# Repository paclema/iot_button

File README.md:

# iot_button

## WARNING: _Repository Discontinued_
This repository is now archived and further development is not expected. The repository was initially created as a proof of concept to develop a firmware for ESP8266 and ESP32 devices capable of running a web server stored into the flash memory next to Arduino based firmware code to handle easily internal configurations such as WiFI credentials and connection settings, MQTT, OTA and more services configurations or user custom class configurations. 

This repository has been archived as a result of the creation of the Platformio [WebConfigServer](https://github.com/paclema/WebConfigServer) library.

## Features:

Web application:
* Angular 10 and Bootstrap 4 web application to configure the device and visualize data.
* Nebular UI Angular lib.
* ng2-charts to visualize WS data graphs on dashboard web server endpoint.
* Gzipped compression to store and serve the Webapp.

Firmware:
* ESP32 support.
* Improved platformio targets and ESP partitions for Wemos D1 mini and Lolin D32 pro and OTA updates.
* Store configs as JSON and certs on SPI Flash File System (SPIFFS).
* AP+STA wifi mode with wifimulti and mDNS support
* FTP server to easily modify files stored on SPIFFS.
* WrapperOTA class to handle OTA updates.
* WrapperWebSockets class to handle WS communication between device and webserver dashboard endpoint.
* MQTT client as QoS2 to detect disconnection and enabled connection using user&pass and/or certificates.
* Added configurable DeepSleep modes for ESP8266.
* Webserver or AsyncWebserver support.
* Enabled lwip NAT features for ESP8266 and ESP32.
* Added configurable NTP server.

## Requirements:

* Wemos D1 mini (ESP8266) or Lolin D32 pro (ESP32).
* push button on RST --> this will triger the push action after restart the board.
* D0 (GPIO16) connected to RST so Deep Sleep can wake up after the sleep time configured.
* CHPD (or EN) to VCC.
* Wemos D1 mini can use USB power or 3v3-5v on 5v pin.

### Add a new configuration object:
1. Update the new object in the configuration file _/data/config.json_
2. Add the struct object in the configuration class _/lib/WebConfigServer/WebConfigServer.h_
3. Update the parse function to link the json object with the class struct in the configuration class _/lib/WebConfigServer/WebConfigServer.cpp_

### Upload _/data_ folder to ESP SPIFFS File System:

Using platformio run the next command: `pio run -t uploadfs`

### Build webserver to _/data_ fodler:
If you can not run angular-cli from platformio PowerShell using windows, activate it with:
Set-ExecutionPolicy -ExecutionPolicy RemoteSigned -Scope CurrentUser

Under _webserver/_ folder:
```console
ng build --prod --optimization=true --outputHashing=none; npm run postbuild
```

To build and upload SPIFFS
```console
cd ./webserver; ng build --prod --optimization=true --outputHashing=none; npm run postbuild;cd ..; pio run --target uploadfs --environment d1_mini
```

To build for xammp:
```console
ng build --prod --optimization=true --outputHashing=none --outputPath=C:/xampp/htdocs --deleteOutputPath=false
```

These build options can be added in angular.json in the future.

### Compress _/data_ fodler with gzip:
Under webserver folder:

```console
npm run postbuild
```

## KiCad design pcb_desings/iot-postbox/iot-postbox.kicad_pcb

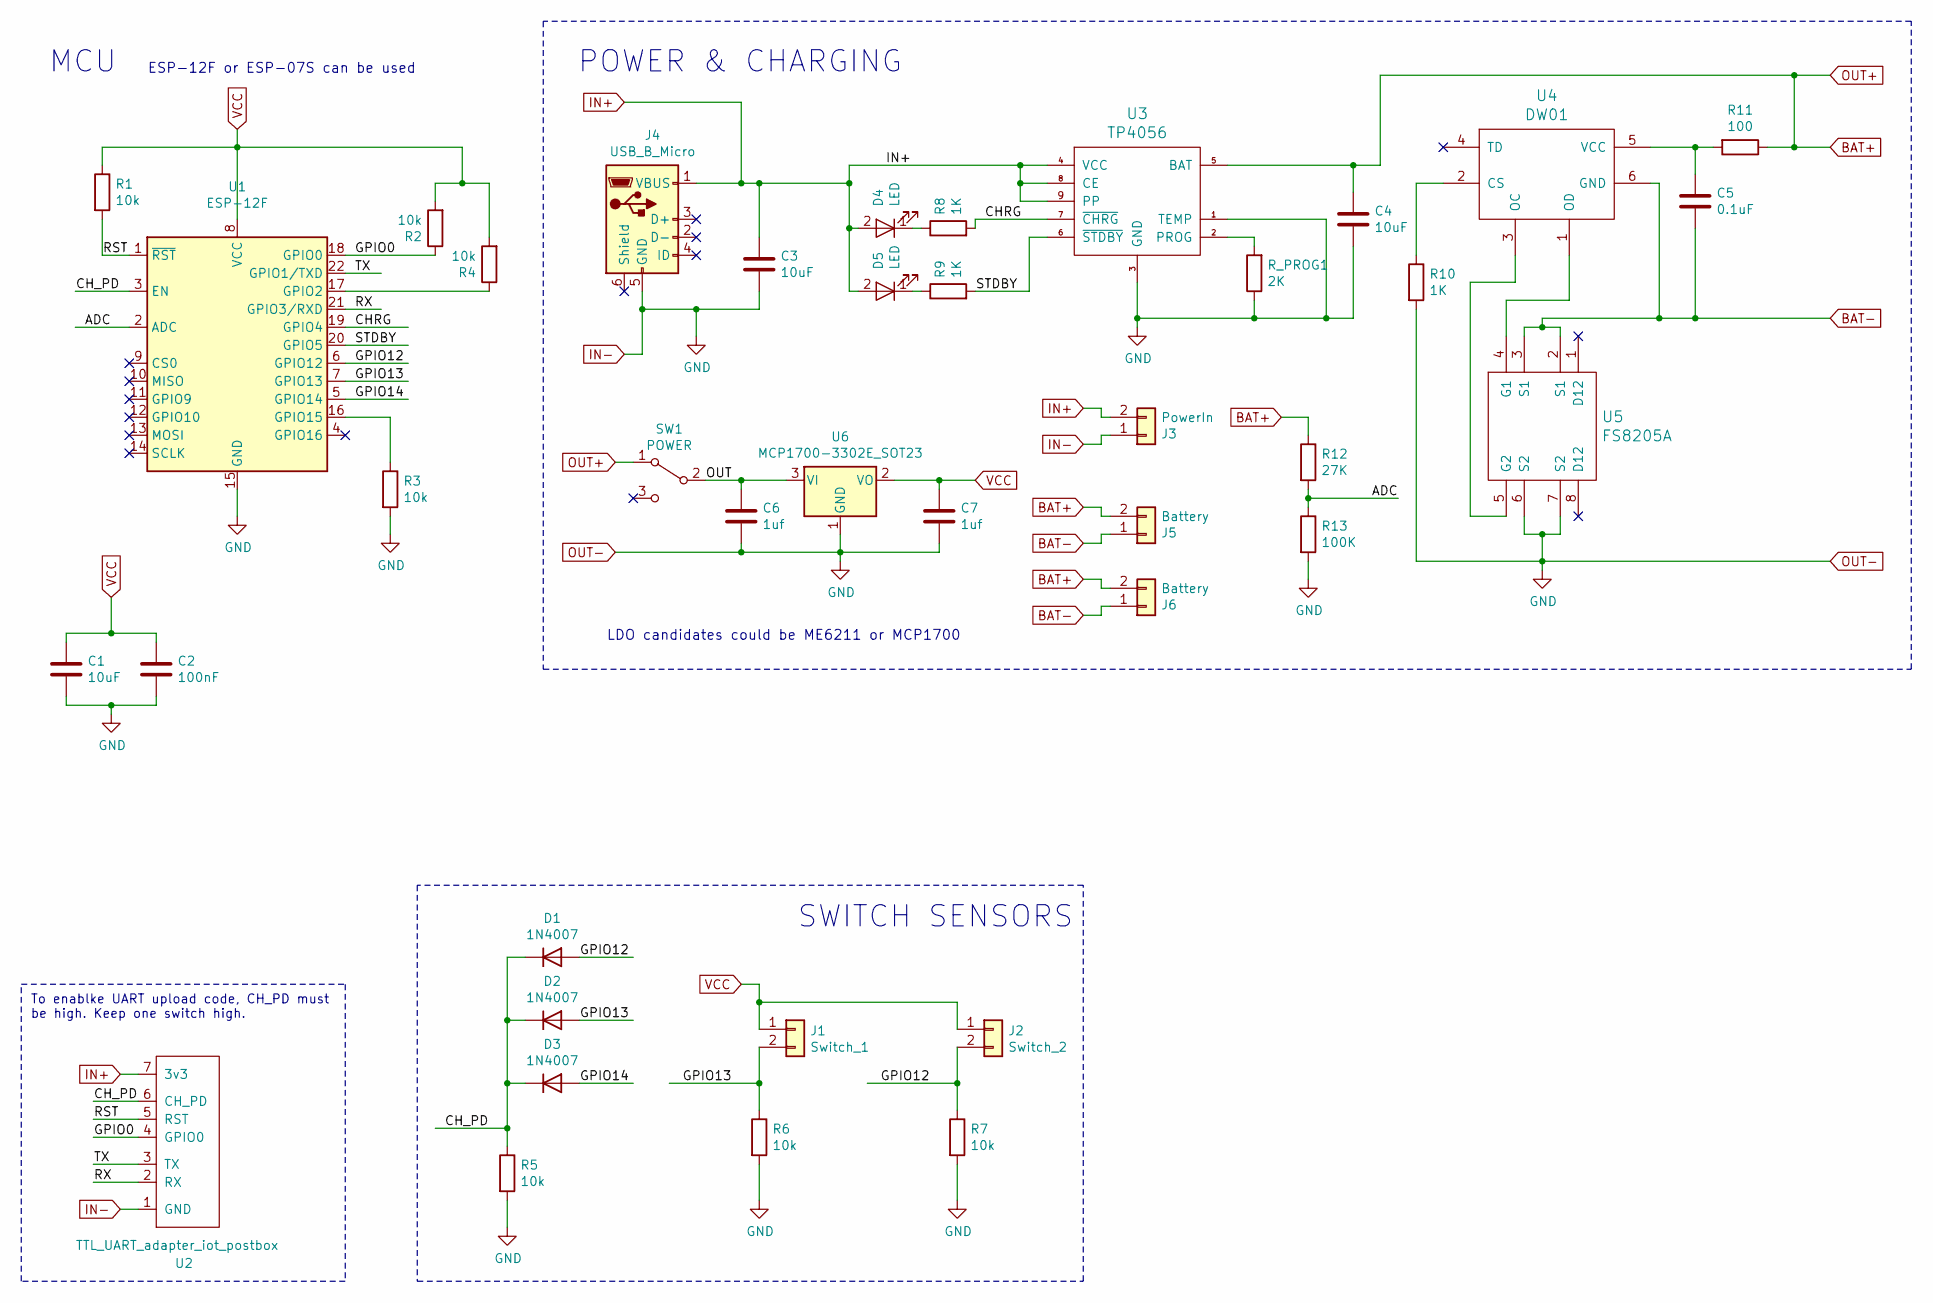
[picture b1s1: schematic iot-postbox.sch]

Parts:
C1, C3, C4: 10uF; C_0805_2012Metric
C2: 100nF; C_0805_2012Metric
C5: 0.1uF; C_0805_2012Metric
C6, C7: 1uf; C_0805_2012Metric
D1, D2, D3: 1N4007; D_SOD-123
D4, D5: LED; LED_0805_2012Metric
J1: Switch_1; PinHeader_1x02_P2.54mm_Vertical
J2: Switch_2; PinHeader_1x02_P2.54mm_Vertical
J3: PowerIn; PinHeader_1x02_P2.54mm_Vertical
J4: USB_B_Micro; USB_Micro-B_Amphenol_10118194_Horizontal
J5: Battery; JST_PH_S2B-PH-SM4-TB_1x02-1MP_P2.00mm_Horizontal
J6: Battery; PinHeader_1x02_P2.54mm_Vertical
R1, R2, R3, R4, R5, R6, R7: 10k; R_0805_2012Metric
R8, R9, R10: 1K; R_0805_2012Metric
R11: 100; R_0805_2012Metric
R12: 27K; R_0805_2012Metric
R13: 100K; R_0805_2012Metric
R_PROG1: 2K; R_0805_2012Metric
SW1: POWER; 1P2T_SPDT_MSK-C02_7pin
U1: ESP-12F; ESP-12E
U2: TTL_UART_adapter_iot_postbox; PinHeader_1x07_P2.54mm_Vertical
U3: TP4056; TP4056_SOP-8-PP
U4: DW01; SOT-23-6_Handsoldering
U5: FS8205A; TSSOP-8_4.4x3mm_P0.65mm
U6: MCP1700-3302E_SOT23; SOT-23

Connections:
/ADC: R12.2, R13.1, U1.2 (ADC)
/CHRG: R8.2, U1.19 (GPIO4), U3.7 (~CHRG)
/CH_PD: D1.1 (K), D2.1 (K), D3.1 (K), R5.1, U1.3 (EN), U2.6 (CH_PD)
/GPIO0: R2.1, U1.18 (GPIO0), U2.4 (GPIO0)
/GPIO12: D1.2 (A), J2.2, R7.1, U1.6 (GPIO12)
/GPIO13: D2.2 (A), J1.2, R6.1, U1.7 (GPIO13)
/GPIO14: D3.2 (A), U1.5 (GPIO14)
/OUT: C6.1, SW1.2 (B), U6.3 (VI)
/RST: R1.2, U1.1 (~RST), U2.5 (RST)
/RX: U1.21 (GPIO3/RXD), U2.2 (RX)
/STDBY: R9.2, U1.20 (GPIO5), U3.6 (~STDBY)
/TX: U1.22 (GPIO1/TXD), U2.3 (TX)
BAT+: C4.1, J5.2, J6.2, R11.1, R12.1, SW1.1 (A), U3.5 (BAT)
BAT-: C5.2, J5.1, J6.1, U4.6 (GND), U5.2 (S1), U5.3 (S1)
IN+: C3.1, D4.2 (A), D5.2 (A), J3.2, J4.1 (VBUS), U2.7 (3v3), U3.4 (VCC), U3.8 (CE), U3.9 (PP); also elsewhere on the board
IN-: C1.2, C2.2, C3.2, C4.2, C6.2, C7.2, J3.1, J4.5 (GND), R3.2, R5.2, R6.2, R7.2, R10.2, R13.2, R_PROG1.1, U1.15 (GND), U2.1 (GND), U3.1 (TEMP), U3.3 (GND), U5.6 (S2), U5.7 (S2), U6.1 (GND)
unnamed: C5.1, R11.2, U4.5 (VCC)
unnamed 17: D4.1 (K), R8.1; also elsewhere on the board
unnamed 18: D5.1 (K), R9.1; also elsewhere on the board
unnamed: R3.1, U1.16 (GPIO15)
unnamed: R4.1, U1.17 (GPIO2)
unnamed: R10.1, U4.2 (CS)
unnamed: R_PROG1.2, U3.2 (PROG)
unnamed: U4.1 (OD), U5.4 (G1)
unnamed: U4.3 (OC), U5.5 (G2)
VCC: C1.1, C2.1, C7.1, J1.1, J2.1, R1.1, R2.2, R4.2, U1.8 (VCC), U6.2 (VO)

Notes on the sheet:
To enablke UART upload code, CH_PD must be high. Keep one switch high.
POWER & CHARGING
SWITCH SENSORS
MCU
ESP-12F or ESP-07S can be used
LDO candidates could be ME6211 or MCP1700

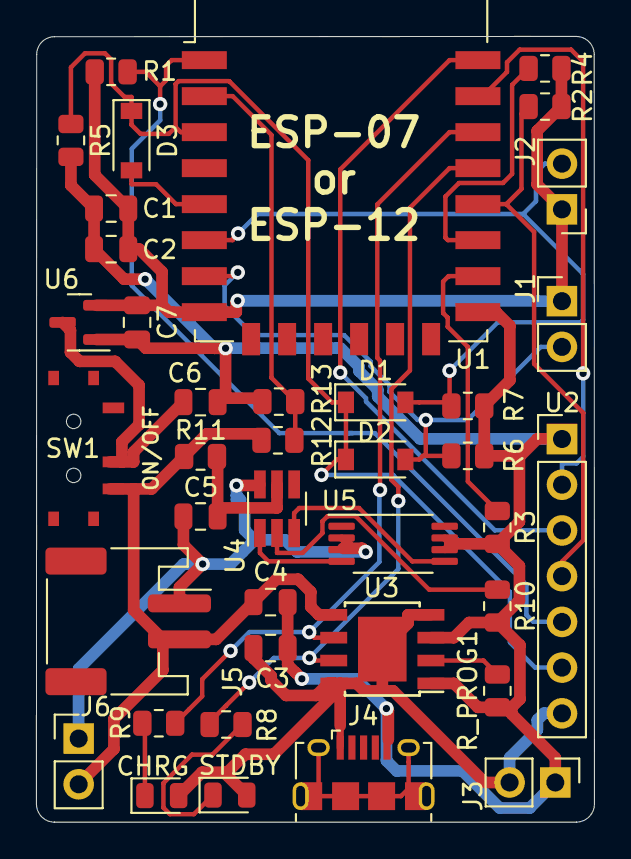
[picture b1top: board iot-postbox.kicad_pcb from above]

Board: 2 copper layers, 31.0 x 43.6 mm, 39 parts (0 on the bottom side), 26 nets.

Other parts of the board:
CHRG: LED; LED_0805_2012Metric
STDBY: LED; LED_0805_2012Metric

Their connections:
IN+: CHRG.2, STDBY.2; also elsewhere on the board
unnamed 17: STDBY.1; also elsewhere on the board
unnamed 18: CHRG.1; also elsewhere on the board

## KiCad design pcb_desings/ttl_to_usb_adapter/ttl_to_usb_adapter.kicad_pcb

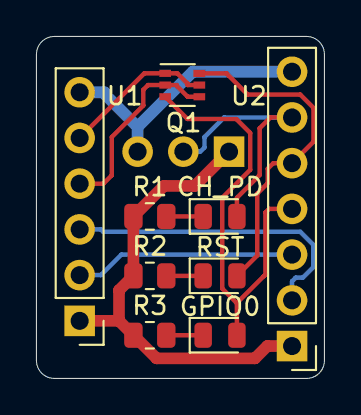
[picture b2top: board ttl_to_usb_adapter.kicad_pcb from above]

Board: 2 copper layers, 16.0 x 19.0 mm, 10 parts (1 on the bottom side), 12 nets.

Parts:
CH_PD: EN; LED_0805_2012Metric
GPIO0: GPIO0; LED_0805_2012Metric
J1: CH_PD_selector; PinHeader_1x03_P2.54mm_Horizontal
Q1: UMH3N; SOT-363_SC-70-6
R1, R2, R3: 68; R_0805_2012Metric
RST: RST; LED_0805_2012Metric
U1: USB_to_TTL; PinHeader_1x06_P2.54mm_Vertical
U2: TTL_UART_adapter_iot_postbox; PinHeader_1x07_P2.54mm_Vertical

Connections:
/3V3: J1.3, U1.6, U2.7
/CH_PD: CH_PD.2, J1.2, U2.6
/DTR: Q1.2, Q1.4, U1.4
/GND: J1.1, R1.1, R2.1, R3.1, U1.1, U2.1
/GPIO0: GPIO0.2, Q1.3, U2.4
/RST: Q1.6, RST.2, U2.5
/RTS: Q1.1, Q1.5, U1.5
/RXD: U1.2, U2.3
/TXD: U1.3, U2.2
unnamed: CH_PD.1, R1.2
unnamed: R2.2, RST.1
unnamed: GPIO0.1, R3.2

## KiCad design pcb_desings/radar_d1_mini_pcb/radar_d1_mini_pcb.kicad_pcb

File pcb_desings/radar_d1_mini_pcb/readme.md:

lib dependencies for kicad:
https://github.com/jerome-labidurie/d1_mini_kicad
https://github.com/rubienr/wemos-d1-mini-kicad
https://kicad.github.io/packages3d/TerminalBlock_Phoenix

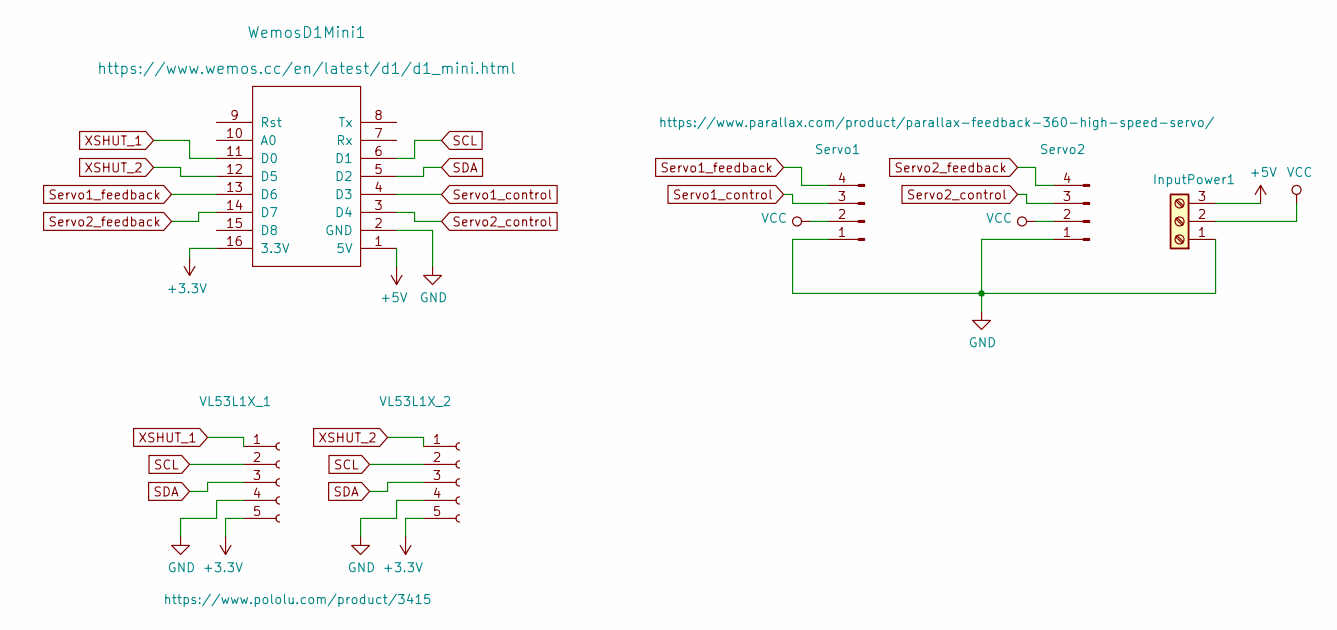
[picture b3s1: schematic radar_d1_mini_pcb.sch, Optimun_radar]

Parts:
InputPower1: Screw_Terminal_01x03; TerminalBlock_Phoenix_MKDS-1,5-3-5.08_1x03_P5.08mm_Horizont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
Servo1, Servo2: Conn_01x04_Male; PinHeader_1x04_P2.54mm_Vertical
VL53L1X_1, VL53L1X_2: Conn_01x05_Female; PinHeader_1x05_P2.54mm_Vertical
WemosD1Mini1: WeMos_D1_mini; D1_mini_board

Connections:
+3V3: VL53L1X_1.5, VL53L1X_2.5, WemosD1Mini1.16 (3.3V)
+5V: InputPower1.3, WemosD1Mini1.1 (5V)
GND: InputPower1.1, Servo1.1, Servo2.1, VL53L1X_1.4, VL53L1X_2.4, WemosD1Mini1.2 (GND)
SCL: VL53L1X_1.2, VL53L1X_2.2, WemosD1Mini1.6 (D1)
SDA: VL53L1X_1.3, VL53L1X_2.3, WemosD1Mini1.5 (D2)
Servo1_control: Servo1.3, WemosD1Mini1.4 (D3)
Servo1_feedback: Servo1.4, WemosD1Mini1.13 (D6)
Servo2_control: Servo2.3, WemosD1Mini1.3 (D4)
Servo2_feedback: Servo2.4, WemosD1Mini1.14 (D7)
VCC: InputPower1.2, Servo1.2, Servo2.2
XSHUT_1: VL53L1X_1.1, WemosD1Mini1.11 (D0)
XSHUT_2: VL53L1X_2.1, WemosD1Mini1.12 (D5)

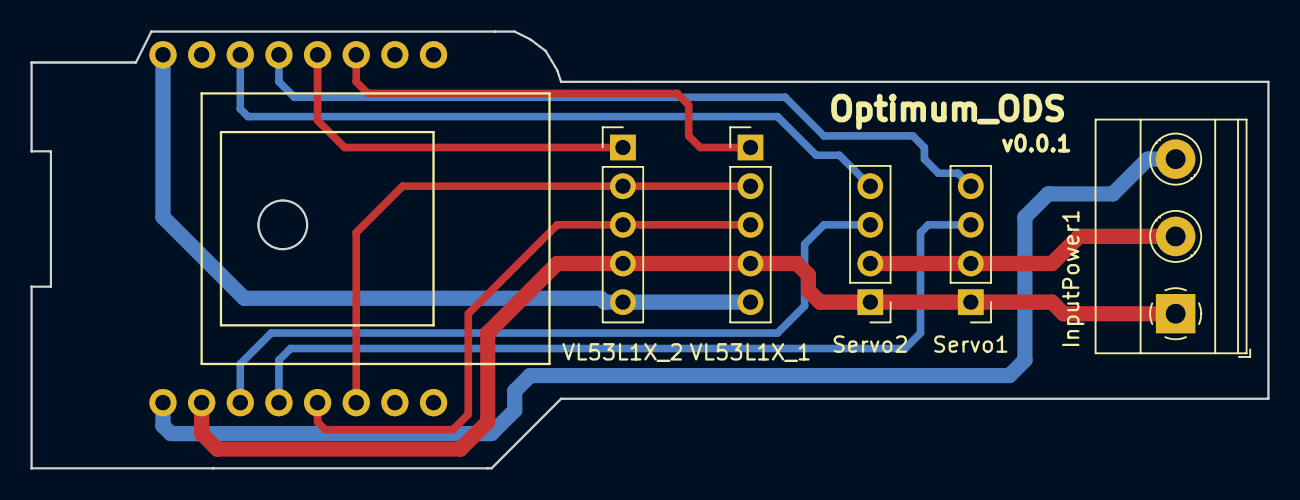
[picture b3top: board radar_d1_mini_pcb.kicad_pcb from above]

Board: 2 copper layers, 81.3 x 28.7 mm, 6 parts (1 on the bottom side), 12 nets.

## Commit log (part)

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2019-06-19 Updated POST for restoreBackup and added file backups management from firmware
2019-06-19 Refactorized code to use WebConfigServer class
2019-06-19 Added favicon on html
2019-06-20 Added ftp server
2019-06-21 Added OTA wrapper class
2019-06-22 Added MQTT client
2019-06-22 toUpperCase first letter for each config name
2019-06-22 Added DeepSleep and LightSleep features
2019-06-22 Code cleaned
2019-06-23 Fixed some variable names and html view for nested objects
2019-06-24 Added platformio lib_deps and moved html deps to upstream
2020-09-03 Replaced SPIFFS deprecated File System to LittleFS
2020-09-04 Updated readme and fixed config ssid variable
2020-09-04 Added AP+STA wifi mode and configs
2020-09-07 Update missing config.json data
2020-09-10 Added loop timers for mqtt publish and sensor reading
2020-09-15 Added VL53L1X readdings
2020-09-16 Added servo control
2020-09-17 Added sensor libraries separatelly for VL53L0X and VL53L1X
2020-09-18 Tried to calculate sensorAngle
2020-09-22 Fixed real angle calculations with servo position
2020-09-25 Added HCSR04 sensor functions
2020-10-16 Added init angular webserver
2020-10-17 Added json import from local file on webserver
2020-10-19 Added boostrap from npm packages and fixed config tabs
2020-10-19 Fixed readme
2020-10-20 Added dev config for ng build
2020-10-20 Added http get request to get the data from config.json file
2020-10-20 Added error handler for http request reading config.json
2020-10-20 removed unnecesary file
2020-10-20 Fixed import throwError
2020-10-20 Init example TDF with testFormModel property
2020-10-21 Add input control state, validation and pattern validation example
2020-10-21 Added display error messages with class binding & ngIf on example forms
2020-10-21 Added select control validation
2020-10-21 Added enrollment service to post submitted form data
2020-10-21 Added alerts for post succeded or not
2020-10-21 Removed unnecessary Observable import
2020-10-22 Created Reactive Form example
2020-10-22 Added nested FormGroup into the Reactive FormGroup
2020-10-22 Use FormBuilder service instead FormGroup and FormControl
2020-10-22 Created a getter to get the FormControl
2020-10-22 Added a factory validator to add forbidden regex strings
2020-10-22 Added Cross field validator for password and confirmPassword
2020-10-23 Refactorized sensorMotorAngle()
2020-10-24 Added FormArray with FormControl dynamically into the FormGroup
2020-10-26 Added buildTabsForm() to build dynamically configTabsForm Reactive Form
2020-10-26 Add enableTutorial property to disable relative tutorial html template
2020-10-26 Added helpers for config type
2020-10-26 Moved buttons to config-tab component
2020-10-26 Displayed error on configTabsForm
2020-10-27 Updated view for tabs Form depending of the config type
2020-10-27 Added /restore_config POST req on backend webserver
2020-10-27 Added alarm for dataMsgPost
2020-10-27 Fixed restoreBackup to get only filename as parameter
2020-10-27 Added /restart API communication
2020-10-27 Fixed ESP webserver http responses
2020-10-27 Removed default values
2020-10-27 Added loading spinner
2020-10-28 Rebase conflicts solved
2020-10-28 Fixed some variables from json config file
2020-10-28 Added MAX_INIT_RETRIES for VL53L1X sensor init
2020-10-28 Added reading servo pos from hacked potentiometer
2020-10-28 Removed sensorMotorAngle() from main loop and moved to sensor Loop
2020-10-28 COnfigure device hostname properly
2020-10-29 Cleaned SensorMotor class adding servo pot feedback values
2020-10-30 Adjust some delays
2020-10-30 Code documented and cleaned
2020-10-30 Added processing radar
2020-11-02 Added Nebular theme, nb-sidebar, dashboard component and update routing
2020-11-03 Fixed toggle sidebar, eva icons & added config-tabs compnnt into nb-card
2020-11-03 Added mqtt queue string to publish list of msg instead only one
2020-11-05 Updated radar_processing to draw multiple lines simultaneously
2020-11-06 Code cleanned and fixed mqttQueueString
2020-11-06 Added publish websocket example from backend server
2020-11-06 Fixed backend wss mesgs using json
2020-11-07 Fixed and documented websocket function on webapp and backend
2020-11-07 Updated webapp to lastest version
2020-11-09 Created WrapperWebSockets class
2020-11-09 Minor fix
2020-11-10 Moved SensorMotor to RadarMotor class
2020-11-10 Removed radarMotorAngle()
2020-11-10 Added RSSI to websockets
2020-11-11 Added ng2-charts
2020-11-12 Fixed chartjs to print heap_free data
2020-11-12 Updated firmware backedn to publish ws in broadcast mode
2020-11-13 Added NB modules and button to show/hidde all chart lines
2020-11-13 Fixed loop_time_ms config and main() & added debug for esp stack trace
2020-11-16 Added FormGroup and Controls for nested configs for each tabs.
2020-11-17 Added Radar webconfigs
2020-11-19 Added VL53L1X debug printing function
2020-11-25 parseWebConfig() now receive just the JsonObject instead the whole doc
2020-11-25 Added sensorDistance & Radar Class using IWebConfig, updated RadarMotor
2020-11-26 Added DistSensor classes and Factory for HCSR04, VL53L0X, VL53L1X & ROI
2020-11-26 Commented removeDistanceSensor() due memory leak issues
2020-11-27 Moved DistSensor variablkes to protected and added set and getters
2020-12-09 Fixed DistSensor setup after new configuration
2020-12-09 Added parseWebConfig() to DistSensor classes
2020-12-11 Added ROI using 4 zones
2020-12-14 Added ROI distances for 4 zones
2020-12-18 Refactorized RadarMotor and Radar to include Parallax servo object
2020-12-29 Added gzip compresion stage for webserver
2020-12-29 Updated firmware to load gziped webapp
2020-12-29 Fixed MQTT reconnect to avoid delays on main loop
2020-12-30 Connect MQTT client with QoS 2 to detect disconnection
2021-01-07 Cleaned websocket functions published
2021-01-07 Updated platformio targets with corresponding libraries
2021-01-08 Fixed loading certs for wifiClientSecure
2021-01-08 Added enable config variable for mqtt
2021-01-08 Added platformio OTA targets
2021-01-11 Updated RadarMotor class to work with ESP32 and Parallax class functions
2021-01-12 Refactorized platformoi lib deps and added radar angle to ws
2021-01-12 Updated servo classes to work with ESP32 and ESP8266
2021-01-14 Organized platformio lib dependencies and added flags to avoid warnings
2021-01-14 Added AsyncWebserver for ESP32 and ESP8266 and updated getContentType()
2021-01-14 Added missing POST request handler for AsyncWebserver
2021-01-15 Fixed large json POST req for /save_config. Added serveStatic() files
2021-01-18 Fixed AsyncWebServer POSTreq using bigger json than defined in AsyncJson
2021-01-21 Added "Type" to DistSensor and factory creates by type instead by name
2021-01-21 Updated Radar class to create/remove DistSensors by type and name
2021-01-22 Added second motor to Radar class
2021-01-22 Fix leak memory when mqtt not connected reseting mqttQueueString buffer
2021-01-26 Moved services to folder. Fixed POSTs apiUrl. Added routing using hash
2021-01-27 Updated config pins for radar
2021-01-28 Added radar pcb design for Wemos D1 mini
2021-01-29 Fixed Parallax360 feedback timeout
2021-01-29 Added gerbers radar pcb v0.0.1 adding 3mm hole
2021-02-01 Fixed saving config button spinner
2021-02-01 Prevent save_config POST if not enough heap memory
2021-02-02 Removed double config.json load at ngOnInit()
2021-02-02 Fixed chiplogo size for app-loading
2021-02-03 Updated compresed webapp
2021-02-10 Added calibration for dist sensor ROI and changed local vl53l1_api lib
2021-02-11 Added PeopleCounter class
2021-02-11 Added more PeopleCounterGestures
2021-02-11 Updated roi zones
2021-03-18 Fixed mqtt statusPerson as json to mqtt topic
2021-03-22 Added gestures person in range start and end
2021-03-22 Added notifyStatusPerson()
2021-03-29 Added smoothed dists
2021-03-29 Added smoothedDist array
2021-03-29 Updated PeopleCounter config.json
2021-03-30 Added mqtt base topic for peopleCounter msgs
2021-03-30 Added max retries connecting to wifi
2021-03-31 Select narrow ROI zones
2021-03-31 Fixed processing origin translation for some drawings
2021-03-31 Update ROI distances if not errors for 2ROI
2021-04-05 Added neopixel example
2021-04-07 Added angle offset as Parallax member
2021-04-08 Add led color for each gesture and disable feature
2021-04-08 Removed unnecessary defines
2021-04-09 Added debug for ledPin
2021-04-09 Changed default led pin config to GPIO13 or D7
2021-04-09 Added configurable roiZones config
2021-04-09 Fixed sensorRead2Roi() using roiZones config
2021-04-09 Moved some ROI msgs only if debug
2021-04-12 Added reedSwitch state in webapp dashboard and notify under /data/reedSwitch mqtt topic
2021-04-13 Fixed reed switch connection diagram and pin input
2021-04-19 Added decode person gesture [0,3,X...]
2021-04-21 Redefined NAPT to IP_NAPT_MAX
2021-04-21 Adde sensor_name to RPoint struct
2021-04-21 Small correction for default pins
2021-04-22 Added processGesture() method to avoid gesture recognition if VL53L1_Error while reading distances
2021-04-22 Configured deep sleep configs
2021-04-22 Added pcb design for iot-postbox
2021-04-22 Added time to sleep as mqtt loop payload
2021-04-22 Updated AP configs
2021-04-30 Enhance print msg
2021-05-02 Fixed _urlBase for API calls
2021-05-02 Improved WS connection, added port from config.json and info toastr msgs
2021-05-02 Added configurable port for WebSocket and WebConfigServer class
2021-05-03 Added configurable enable_NAT network property
2021-05-03 Fixed get sta channel for esp8266
2021-05-03 Updated data webserver to v0.0.1
2021-05-03 Small fix serial command and Adafruit_VL53L0X dependency
2021-05-06 Added loop delay for ZoneDistances struct. Fix mqtt buffer sizes and only publish non-zero ZoneDistances
2021-05-07 Add buffer and publish ZoneDistances after gesture
2021-05-07 Added configurable NTP
2021-05-07 Added timestamp to mqtt zoneDistances payload
2021-05-12 Fix compability ROI with ESP32
2021-05-20 Updated peopleCounter board sch
2021-05-30 Bump ws from 7.3.1 to 7.4.6 in /webserver/backend
    Bumps [ws](https://github.com/websockets/ws) from 7.3.1 to 7.4.6.
    - [Release notes](https://github.com/websockets/ws/releases)
    - [Commits](https://github.com/websockets/ws/compare/7.3.1...7.4.6)
2021-06-01 Added PostBox functions to setup 2 pins interrupts and mqtt mesage publish
2021-06-01 Updated deepSleepHandler()
2021-06-03 Updated VL53L1X distances reported if OutOfBoundsFail status
2021-06-30 Added config.json for ESP32 mini
2021-07-06 Added ttl_to_usb_adapter pcb board designs
2021-07-06 Removed kicad lib dep
2021-07-06 Added kicad tp4056 lib
2021-07-08 Added ttl_to_usb_adapter board and exported pcbs panelized
2021-07-19 Publish gps and co2 sensor data over mqtt
2021-07-21 Change init GPS and SCD30 order
2021-08-02 Updated main code to suport iotpostbox pcb with tp4056 feedback
2021-08-02 Added vcc post to ws dashboard
2021-08-03 Added esp12e and esp07s platformio targets
2021-08-04 Updated libs and use LinkedList instead SimpleList
2021-08-09 Ported lib dependencies and code to use WebConfigServer lib
2021-08-10 Removed Radar files
2021-08-10 Update mqtt topics
2022-02-11 Bump karma from 5.0.9 to 6.3.14 in /webserver
    Bumps [karma](https://github.com/karma-runner/karma) from 5.0.9 to 6.3.14.
    - [Release notes](https://github.com/karma-runner/karma/releases)
    - [Changelog](https://github.com/karma-runner/karma/blob/master/CHANGELOG.md)
    - [Commits](https://github.com/karma-runner/karma/compare/v5.0.9...v6.3.14)
    ---
    updated-dependencies:
2022-06-03 Bump @angular/core from 10.1.6 to 11.0.5 in /webserver
    Bumps [@angular/core](https://github.com/angular/angular/tree/HEAD/packages/core) from 10.1.6 to 11.0.5.
    - [Release notes](https://github.com/angular/angular/releases)
    - [Changelog](https://github.com/angular/angular/blob/main/CHANGELOG.md)
    - [Commits](https://github.com/angular/angular/commits/11.0.5/packages/core)
    ---
    updated-dependencies:
